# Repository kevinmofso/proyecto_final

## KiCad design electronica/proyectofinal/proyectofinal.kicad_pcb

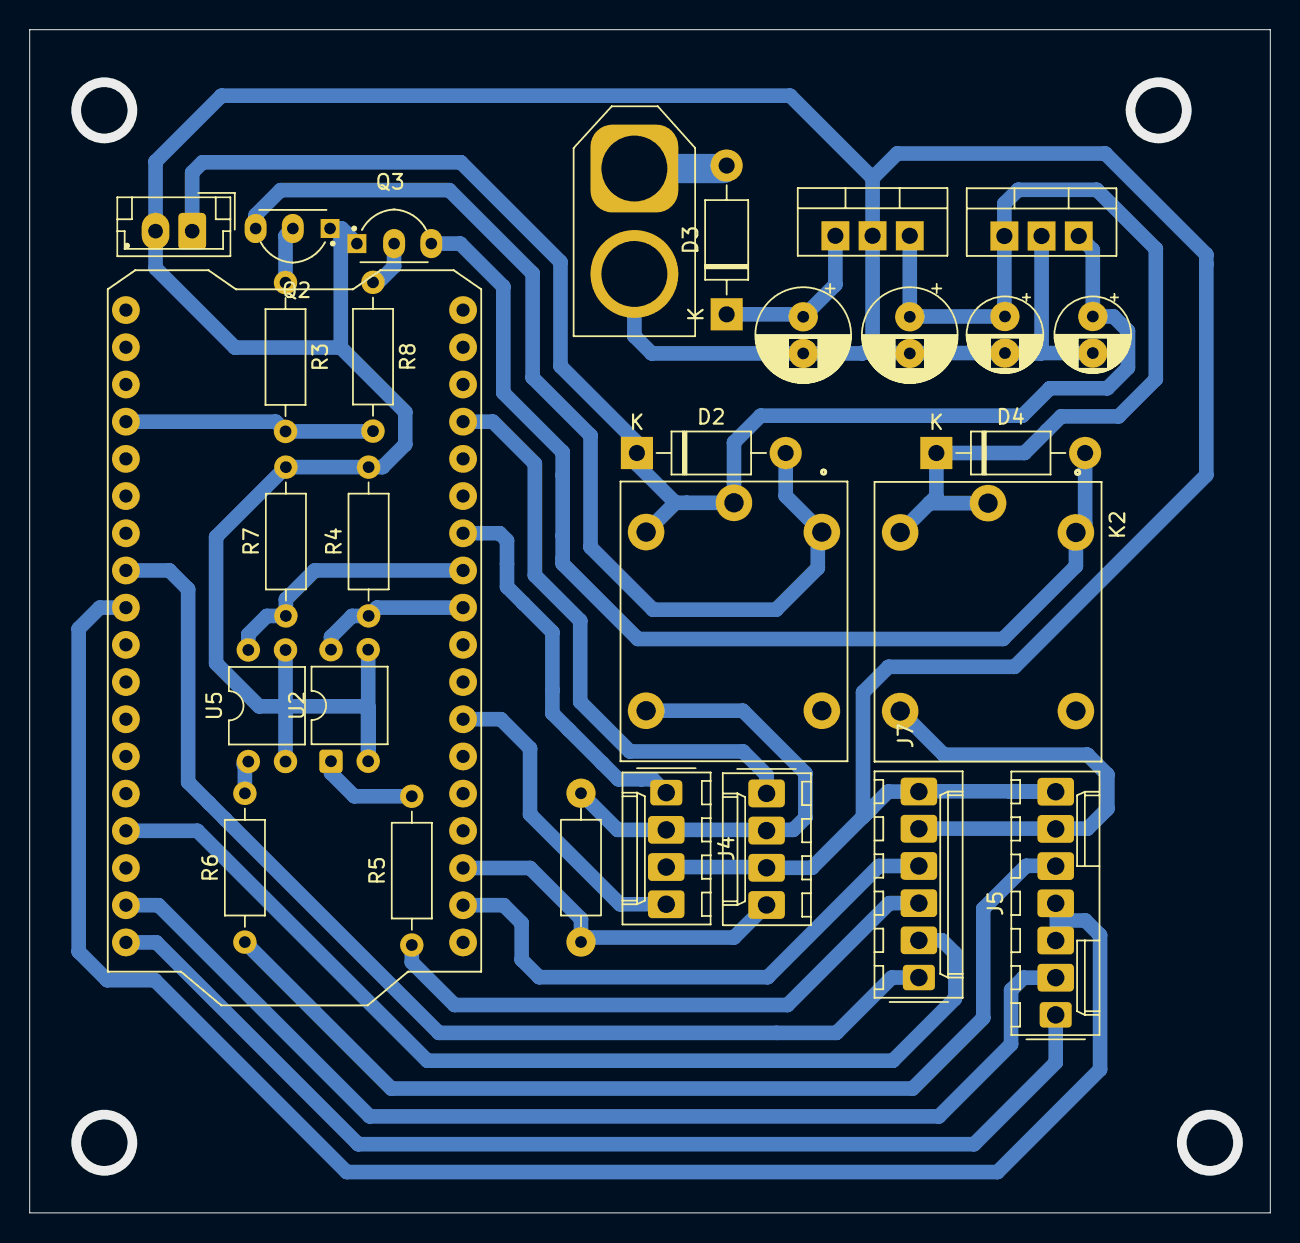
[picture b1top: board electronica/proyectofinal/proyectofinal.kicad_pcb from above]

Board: 2 copper layers, 84.7 x 80.8 mm, 29 parts (0 on the bottom side), 28 nets.

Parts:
C1, C3: 100uf/25v; CP_Radial_D6.3mm_P2.50mm
C2, C4: 10uf/25v; CP_Radial_D5.0mm_P2.50mm
D2, D3, D4: 1N4007; D_DO-41_SOD81_P10.16mm_Horizontal
J1: cnn; AMASS_XT60-F_1x02_P7.20mm_Vertical
J2: conector alimentacion esp; JST_EH_B2B-EH-A_1x02_P2.50mm_Vertical
J3: dht22; Molex_KK-254_AE-6410-04A_1x04_P2.54mm_Vertical
J4: Guva-s12s; Molex_KK-254_AE-6410-04A_1x04_P2.54mm_Vertical
J5: convertidor_TTL; Molex_KK-254_AE-6410-07A_1x07_P2.54mm_Vertical
J7: Conn_01x06_Pin; Molex_KK-254_AE-6410-06A_1x06_P2.54mm_Vertical
K1: SRD-03VDC-SL-C; RELAY_SRD-05VDC-SL-C
K2: SRD-05VDC-SL-C; RELAY_SRD-05VDC-SL-C
Q2, Q3: 2N2222A; TO92254P470H750-3
R1, R4, R7: 30k; R_Axial_DIN0207_L6.3mm_D2.5mm_P10.16mm_Horizontal
R3, R5, R6, R8: 330; R_Axial_DIN0207_L6.3mm_D2.5mm_P10.16mm_Horizontal
U1: LM7833_TO220; TO-220-3_Vertical
U2, U5: PC817; DIP-4_W7.62mm
U3: LM7805_TO220; TO-220-3_Vertical
U4: ESP32_LORA_V2.0; MODULE_ESP32_LORA_V2.0

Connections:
+3.3V: C2.1, D2.1 (K), J2.1, K1.A2, K1.COM, U1.3 (VO)
+3.3V sensores: J3.2, J4.2, K1.NO, R1.2
+5V: C1.1, C4.1, D4.1 (K), K2.A2, K2.COM, U1.1 (VI), U3.3 (VO)
+5V sensores: J5.6, J7.5, K2.NO
DE/RE_TTL: J5.3, J5.4, U4.J2_9 (UO_RTS/V_SPI_QP/GPIO22/SCL/22)
DI_TTL: J5.2, U4.J2_17 (U2_TXD/GPIO17/17)
GND: C1.2, C2.2, C3.2, C4.2, J1.2, J2.2, J3.3, J4.3, J5.7, J7.6, Q2.1, Q3.1, R4.2, R7.2, U1.2 (GND), U2.2, U2.3, U3.2 (GND), U5.2, U5.3
unnamed: D2.2 (A), K1.A1
unnamed: D3.2 (A), J1.1
unnamed: C3.1, D3.1 (K), U3.1 (VI)
unnamed: D4.2 (A), K2.A1, Q3.3
unnamed: Q2.2, R3.1
unnamed: Q3.2, R8.1
unnamed: R5.2, U2.1
unnamed: R6.2, U5.1
RO_TTL: J5.1, U4.J2_18 (OLED_RST/U2_RXD/GPIO16/16)
SIG_Co_MICS-6814: J7.1, U4.J2_8 (PRG_BUTTON/TOUCH1/ADC2_1/GPIO0/0)
SIG_DHT22: J3.4, R1.1, U4.J3_16 (TOUCH5/ADC2_5/GPIO12/12)
SIG_Guva-s12s: J4.4, U4.J3_12 (LED/DAC2/ADC2_8/GPIO25/25)
SIG_N02_MICS-6814: J7.4, U4.J3_17 (TOUCH4/ADC2_4/GPIO13/13)
SIG_NH3_MICS-6814: J7.2, U4.J2_15 (TOUCH2/HSPI_WP/ADC2_2/GPIO2/2)
bool mics: J7.3, R5.1
bool ttl: J5.5, R6.1
pin Guva-s12s: J4.1, U4.J3_7 (ADC1_3/GPI39/39)
pin dht: J3.1, U4.J3_4 (ADC1_0/GPI36/36)
pin ttl: R7.1, U4.J3_8 (LORA_DIO2/ADC1_6/GPI34/34), U5.4
pinmics: R4.1, U2.4, U4.J3_9 (LORA_DIO1/ADC1_7/GPI35/35)
vext: R3.2, R8.2, U4.J2_4 (VEXT)

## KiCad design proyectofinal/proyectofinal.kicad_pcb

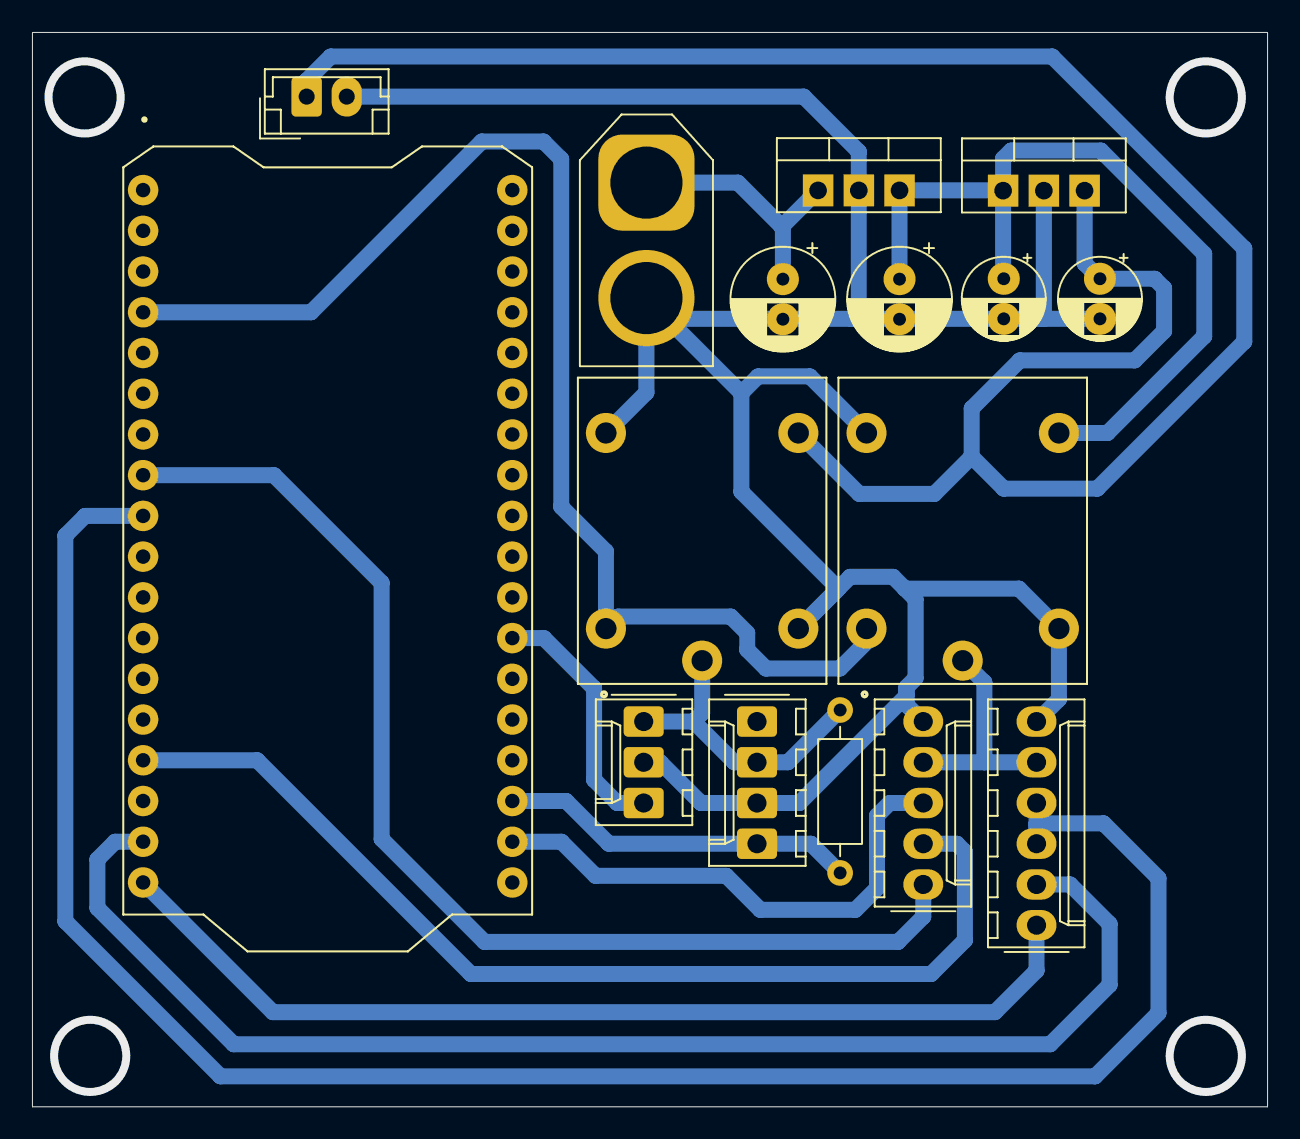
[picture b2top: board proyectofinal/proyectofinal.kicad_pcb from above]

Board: 2 copper layers, 77.0 x 67.0 mm, 16 parts (0 on the bottom side), 15 nets.

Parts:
C1, C3: 100uf/25v; CP_Radial_D6.3mm_P2.50mm
C2, C4: 10uf/25v; CP_Radial_D5.0mm_P2.50mm
J1: cnn; AMASS_XT60-F_1x02_P7.20mm_Vertical
J2: conector alimentacion esp; JST_EH_B2B-EH-A_1x02_P2.50mm_Vertical
J3: dht22; Molex_KK-254_AE-6410-04A_1x04_P2.54mm_Vertical
J4: Guva-s12s; Molex_KK-254_AE-6410-03A_1x03_P2.54mm_Vertical
J5: convertidor_TTL; Molex_KK-254_AE-6410-06A_1x06_P2.54mm_Vertical
J6: MICS-6814; Molex_KK-254_AE-6410-05A_1x05_P2.54mm_Vertical
K1: rele 3.3v; RELAY_SRD-05VDC-SL-C
K2: rele 5v; RELAY_SRD-05VDC-SL-C
R1: 30k; R_Axial_DIN0207_L6.3mm_D2.5mm_P10.16mm_Horizontal
U1: LM7833_TO220; TO-220-3_Vertical
U3: LM7805_TO220; TO-220-3_Vertical
U4: ESP32_LORA_V2.0; MODULE_ESP32_LORA_V2.0

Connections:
+3.3V: C2.1, J2.1, K1.NO, U1.3 (VO)
+3.3V sensores: J3.2, J4.1, K1.COM, R1.2
+5V: C1.1, C4.1, K2.NO, U1.1 (VI), U3.3 (VO)
+5V sensores: J5.5, J6.4, K2.COM
DE/RE_TTL: J5.3, J5.4, U4.J2_9 (UO_RTS/V_SPI_QP/GPIO22/SCL/22)
DI_TTL: J5.2, U4.J2_17 (U2_TXD/GPIO17/17)
GND: C1.2, C2.2, C3.2, C4.2, J1.2, J2.2, J3.3, J4.2, J5.6, J6.5, K1.A2, K1.NC, K2.A2, K2.NC, U1.2 (GND), U3.2 (GND)
unnamed: C3.1, J1.1, U3.1 (VI)
RO_TTL: J5.1, U4.J2_18 (OLED_RST/U2_RXD/GPIO16/16)
SIG_Co_MICS-6814: J6.1, U4.J2_8 (PRG_BUTTON/TOUCH1/ADC2_1/GPIO0/0)
SIG_DHT22: J3.4, R1.1, U4.J3_16 (TOUCH5/ADC2_5/GPIO12/12)
SIG_Guva-s12s: J4.3, U4.J3_12 (LED/DAC2/ADC2_8/GPIO25/25)
SIG_N02_MICS-6814: J6.3, U4.J3_17 (TOUCH4/ADC2_4/GPIO13/13)
SIG_NH3_MICS-6814: J6.2, U4.J2_15 (TOUCH2/HSPI_WP/ADC2_2/GPIO2/2)
vext: K1.A1, K2.A1, U4.J2_4 (VEXT)

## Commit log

2025-05-28 e
    e
2025-05-30 minimas
    minimas
2025-06-04 w
    w
2025-06-04 s
    s
2025-06-05 k
    l
2025-06-06 1
    1
2025-06-13 le cambie la resistencia de pullup del dht22
    le cambie la resistencia de pullup del dht22
2025-06-13 loisto
    st
2025-07-11 1
    uni algunos codigos asi ya puede mandar el lora lecturas de algo
2025-07-11 1
    1113
2025-07-11 Create lora_dht
2025-07-13 b
    b
2025-07-18 Update mq-135_DHT22_LORA_HOLA.ino
    anda perfecto
2025-09-04 Create npk
2025-09-19 Create npk con heltec
2025-10-03 Create nueva placa
2025-10-08 Update nueva placa
    anda bien , dht lora y mq
2025-10-20 nueva placa
    Updated comments and improved readability in the code.
2025-10-20 Update nueva placa
2025-11-27 orden
    ordene todo cada sensoor en una carpeta
2025-11-27 orden
    organize los folders y los nombre dependiendo de su funcion
2026-01-07 agregue V2
    juente la parte de easyeda *V2*
